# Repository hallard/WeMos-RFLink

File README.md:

Do you want to turn on / off your TV, AirCon (AC) using Amazon Alexa? Checkout my latest project https://irdevkit.com/RFLink ESP8266 WeMos Shield
============================

This shield is used to hold [RFLink][4] Software with WeMos ESP8266 boards it has just few minimal features.
- I2C Pullups placement
- Classic I2C 128x64 OLED connector
- Placement for Aurel RF transceiver [RTX-MID-3V][5] module
- Placement for choosing single Wire, SMA or u-FL Antenna type
- WS2812B Type LED for visual indication

You can find more information on WeMos on their [site][1], it's really well documented.
I now use WeMos boards instead of NodeMCU's one because they're just smaller, features remains the same, but I also suspect WeMos regulator far better quality than the one used on NodeMCU that are just fake of originals AMS117 3V3.

**Boards are ordered as testing from OSHPark, I did not fully tested them yet, I will update as soon has I got them in my hands. Use at your own risks**

Detailed Description
====================

Look at the schematics for more informations.

### Schematic  

### Boards  
&nbsp;
&nbsp; 

You can order the PCB of this board v1.1 at [OSHPARK][3]

### Assembled boards

I'm currently waiting for boards from OSHPARK

## License WeMos-RFLink

You can do whatever you like with this design.

## Misc
See news and other projects on my [blog][2] 
 
[1]: http://www.wemos.cc/wiki/doku.php?id=en:d1_mini
[2]: https://hallard.me
[3]: https://oshpark.com/shared_projects/KuYqTIB7
[4]: https://sourceforge.net/projects/rflink/
[5]: http://www.tme.eu/gb/details/rtx-mid-3v/aurel-rf-communication-modules/aurel/650201033g/

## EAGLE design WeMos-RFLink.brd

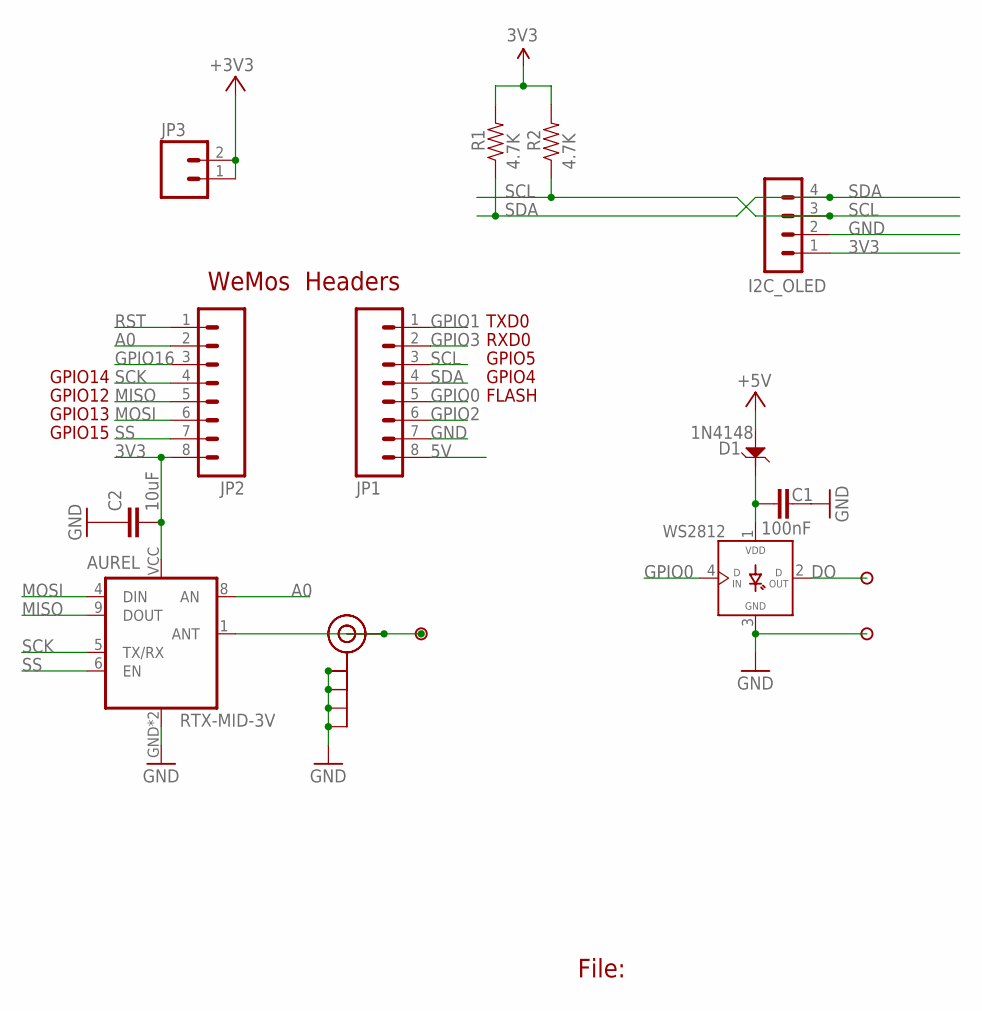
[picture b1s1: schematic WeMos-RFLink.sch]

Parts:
AUREL: RTX-MID-3V; RTX-MID
C1: 100nF; 0805-CAP
C2: 10uF; 0805-CAP-LARGEPADS
D1: 1N4148; SOD123-2.7X1.6
I2C_OLED: CON_HEADER_1X04'SMALL''; M1X4
J$1: SMA_EDGE; SMA-EDGE
JP1, JP2: M08NO_SILK_FEMALE_PTH; 1X08_NO_SILK
JP3: M021X02_NO_SILK; 1X02_NO_SILK
P1: PADSMALL; PAD-SMALL
P2, P3: PADNORMAL; PAD
R1, R2: 4.7K; 0805-RES
U-FL: U.FL
WS2812: WS2812B

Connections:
3V3: AUREL.VCC, C2.2, I2C_OLED.1, JP2.8, JP3.1, JP3.2, R1.2, R2.2
5V: D1.1, JP1.8
A0: AUREL.8 (AN), JP2.2
ANT: AUREL.1 (ANT), J$1.SIG (SIGNAL), P1.1, U-FL.3 (SIGNAL)
DO: P2.1, WS2812.2 (DOUT)
GND: AUREL.GND, AUREL.GND1 (GND), C1.2, C2.1, I2C_OLED.2, J$1.GND@0 (GND), J$1.GND@1 (GND), J$1.GND@2 (GND), J$1.GND@3 (GND), JP1.7, P3.1, U-FL.1 (GND), U-FL.2 (GND), WS2812.3 (GND)
GPIO0: JP1.5, WS2812.4 (DIN)
GPIO1: JP1.1
GPIO2: JP1.6
GPIO3: JP1.2
GPIO16: JP2.3
MISO: AUREL.9 (DOUT), JP2.5
MOSI: AUREL.4 (DIN), JP2.6
RST: JP2.1
SCK: AUREL.5 (TX/RX), JP2.4
SCL: I2C_OLED.3, JP1.3, R2.1
SDA: I2C_OLED.4, JP1.4, R1.1
SS: AUREL.6 (EN), JP2.7
VLED: C1.1, D1.2, WS2812.1 (VDD)

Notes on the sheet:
File:
FLASH
GPIO12
GPIO4
GPIO5
RXD0
TXD0
GPIO13
GPIO14
GPIO15
WeMos Headers

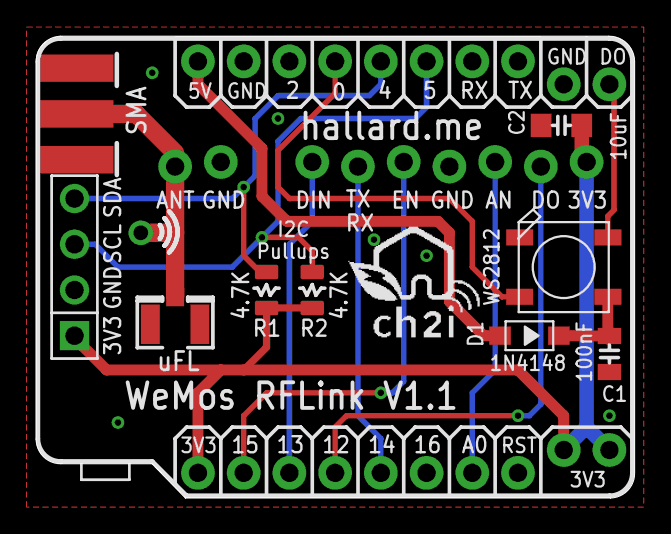
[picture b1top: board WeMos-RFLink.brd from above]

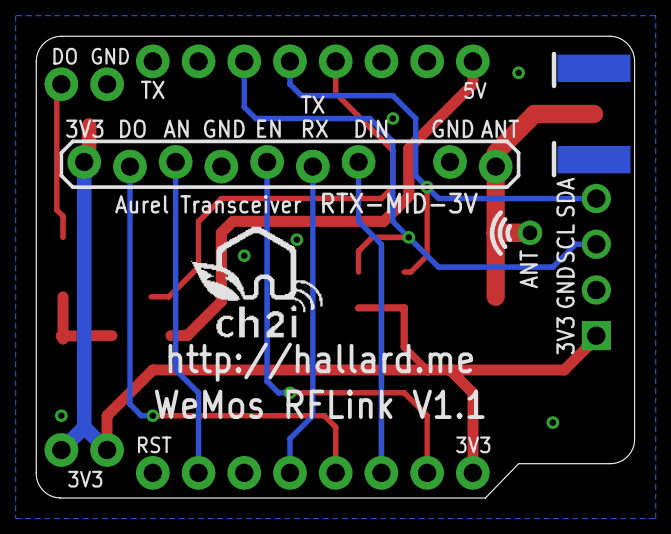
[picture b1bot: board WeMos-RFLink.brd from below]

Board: 2 copper layers, 33.2 x 25.7 mm, 18 parts (2 on the bottom side), 14 nets.

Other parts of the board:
U$1, U$2: LOGO_CH2I_75MM

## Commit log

2016-03-02 Creation
2016-03-02 Added OSHPark Link
2016-03-02 V1.1 Transceiver on bottom shield + RGB LED
2016-03-02 V1.1 Link
2019-10-23 Fix formatting

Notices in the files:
parts and their libraries:
SparkFun-Connectors: Licensing: Creative Commons ShareAlike 4.0 International - https://creativecommons.org/licenses/by-sa/4.0
microbuilder: This work is placed in the public domain, and may be freely used for commercial and non-commercial work with the following conditions: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
